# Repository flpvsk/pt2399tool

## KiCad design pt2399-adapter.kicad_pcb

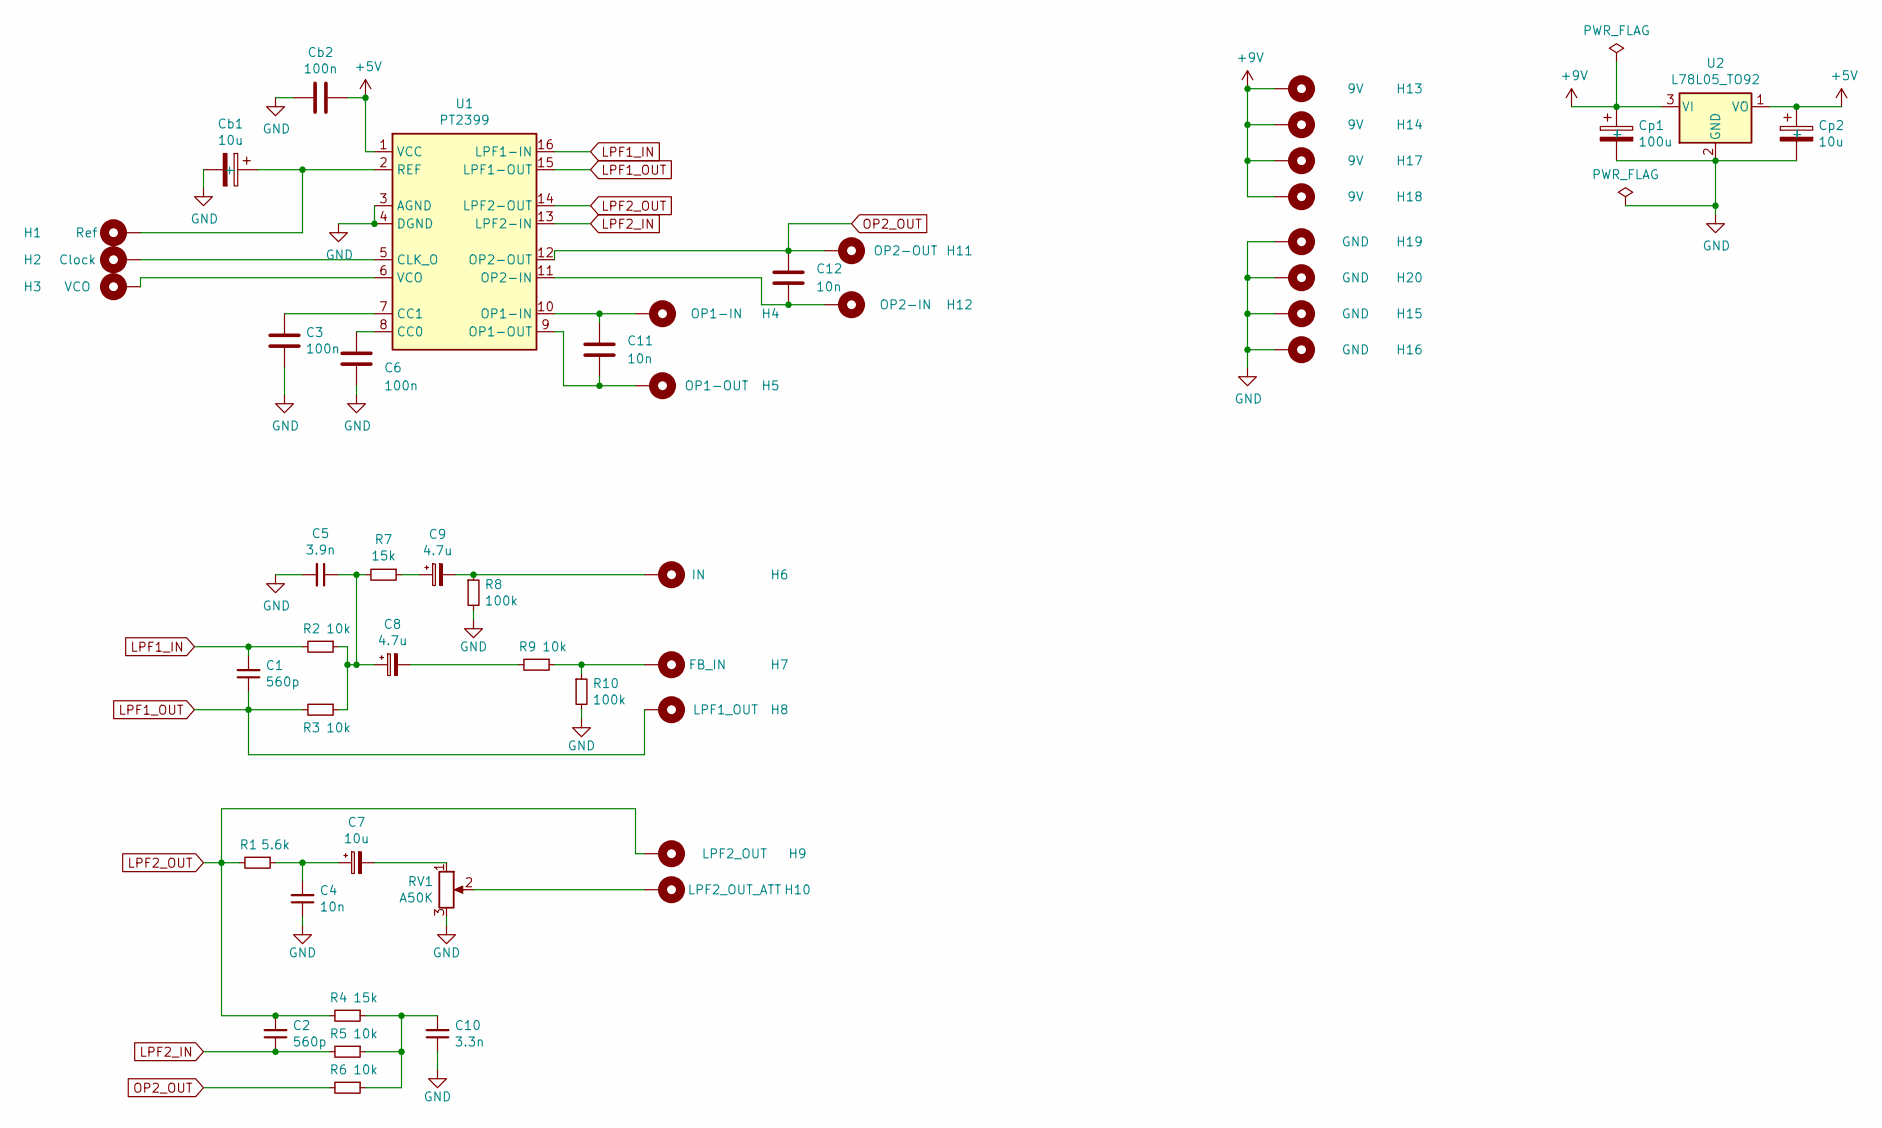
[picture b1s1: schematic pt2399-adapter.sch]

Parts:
C1, C2: 560p; C_0805_2012Metric_Pad1.15x1.40mm_HandSolder; LCSC C159763
C3, C6: 100n; C_0805_2012Metric_Pad1.15x1.40mm_HandSolder; LCSC C49678
C4, C11, C12: 10n; C_0805_2012Metric_Pad1.15x1.40mm_HandSolder; LCSC C1710
C5: 3.9n; C_0603_1608Metric_Pad1.05x0.95mm_HandSolder; LCSC C170145
C7: 10u; C_Elec_4x5.4; LCSC C134721
C8, C9: 4.7u; C_Elec_4x5.4; LCSC C249783
C10: 3.3n; C_0805_2012Metric_Pad1.15x1.40mm_HandSolder; LCSC C53175
Cb1: 10u; C_Elec_4x5.4; LCSC C134721
Cb2: 100n; C_0805_2012Metric_Pad1.15x1.40mm_HandSolder; LCSC C49678
Cp1: 100u; C_Elec_6.3x5.4; LCSC C134723
Cp2: 10u; C_Elec_4x5.4; LCSC C134721
H1: Ref; PinHeader_1x01_P2.54mm_Long_Front_Back
H2: Clock; PinHeader_1x01_P2.54mm_Long_Front_Back
H3: VCO; PinHeader_1x01_P2.54mm_Long_Front_Back
H4: OP1-IN; PinHeader_1x01_P2.54mm_Long_Front_Back
H5: OP1-OUT; PinHeader_1x01_P2.54mm_Long_Front_Back
H6: IN; PinHeader_1x01_P2.54mm_Long_Front_Back
H7: FB_IN; PinHeader_1x01_P2.54mm_Long_Front_Back
H8: LPF1_OUT; PinHeader_1x01_P2.54mm_Long_Front_Back
H9: LPF2_OUT; PinHeader_1x01_P2.54mm_Long_Front_Back
H10: LPF2_OUT_ATT; PinHeader_1x01_P2.54mm_Long_Front_Back
H11: OP2-OUT; PinHeader_1x01_P2.54mm_Long_Front_Back
H12: OP2-IN; PinHeader_1x01_P2.54mm_Long_Front_Back
H13, H14, H17, H18: 9V; PinHeader_1x01_P2.54mm_Long_Front_Back
H15, H16, H19, H20: GND; PinHeader_1x01_P2.54mm_Long_Front_Back
R1: 5.6k; R_0603_1608Metric_Pad1.05x0.95mm_HandSolder
R2, R3, R5, R6, R9: 10k; R_0603_1608Metric_Pad1.05x0.95mm_HandSolder
R4, R7: 15k; R_0603_1608Metric_Pad1.05x0.95mm_HandSolder
R8, R10: 100k; R_0603_1608Metric_Pad1.05x0.95mm_HandSolder
RV1: A50K; 9MM_METAL_SHAFT
U1: PT2399; DIP-16_W7.62mm
U2: L78L05_TO92; TO-92_Inline

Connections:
+5V: Cb2.1, Cp2.1 (+), U1.1 (VCC), U2.1 (VO)
+9V: Cp1.1 (+), H13.1, H14.1, H17.1, H18.1, U2.3 (VI)
GND: C3.1, C4.1, C5.2, C6.1, C10.1, Cb1.2 (-), Cb2.2, Cp1.2 (-), Cp2.2 (-), H15.1, H16.1, H19.1, H20.1, R8.2, R10.2, RV1.3, U1.3 (AGND), U1.4 (DGND), U2.2 (GND)
LPF1_IN: C1.2, R2.2, U1.16 (LPF1-IN)
LPF1_OUT: C1.1, H8.1, R3.2, U1.15 (LPF1-OUT)
LPF2_IN: C2.1, R5.2, U1.13 (LPF2-IN)
LPF2_OUT: C2.2, H9.1, R1.2, R4.2, U1.14 (LPF2-OUT)
unnamed: C3.2, U1.7 (CC1)
unnamed: C4.2, C7.1, R1.1
unnamed: C5.1, C8.1, R2.1, R3.1, R7.2
unnamed: C6.2, U1.8 (CC0)
unnamed: C7.2, RV1.1
unnamed: C8.2, R9.2
unnamed: C9.1, R7.1
unnamed: C9.2, H6.1, R8.1
unnamed: C10.2, R4.1, R5.1, R6.1
unnamed: C11.1, H5.1, U1.9 (OP1-OUT)
unnamed: C11.2, H4.1, U1.10 (OP1-IN)
unnamed: C12.1, H12.1, U1.11 (OP2-IN)
unnamed: Cb1.1 (+), H1.1, U1.2 (REF)
unnamed: H2.1, U1.5 (CLK_O)
unnamed: H3.1, U1.6 (VCO)
unnamed: H7.1, R9.1, R10.1
unnamed: H10.1, RV1.2
OP2_OUT: C12.2, H11.1, R6.2, U1.12 (OP2-OUT)

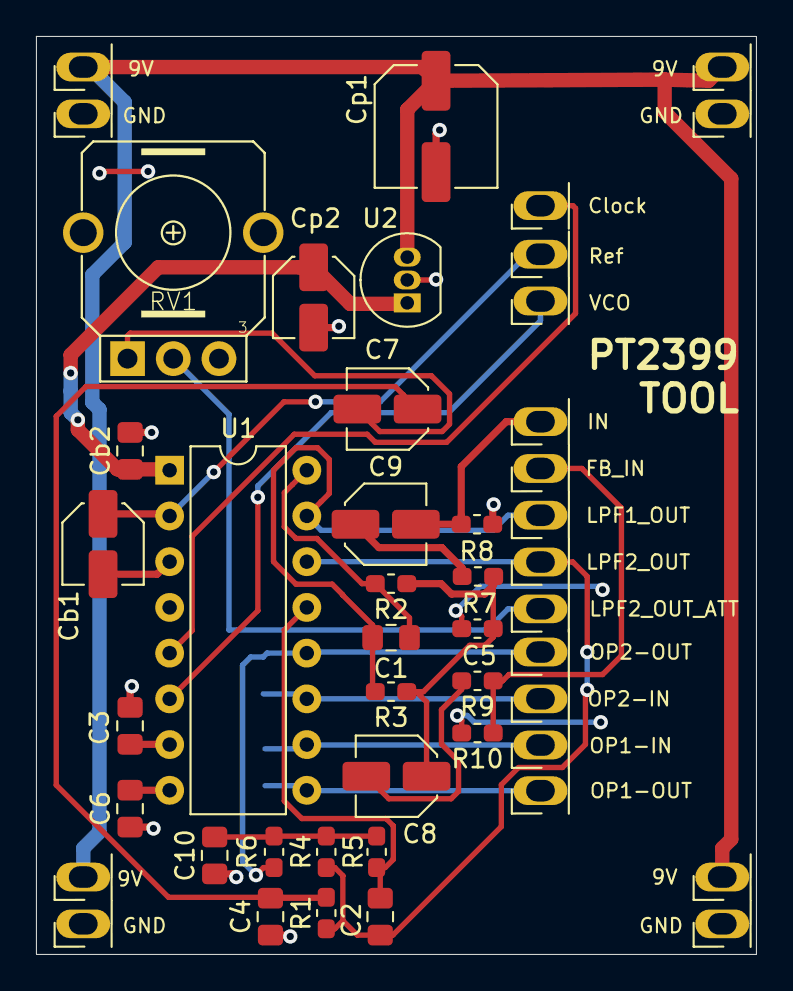
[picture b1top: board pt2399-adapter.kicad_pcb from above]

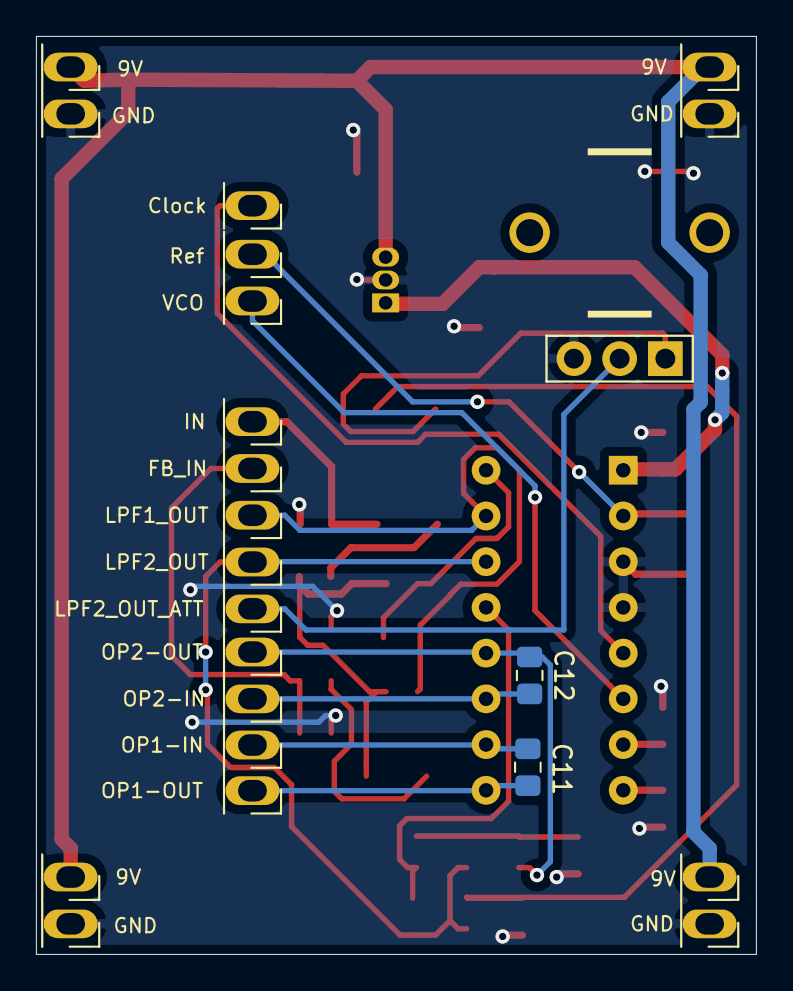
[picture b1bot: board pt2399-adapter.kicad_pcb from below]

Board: 2 copper layers, 40.0 x 51.0 mm, 49 parts (3 on the bottom side), 25 nets.

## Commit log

2021-09-14 Init
